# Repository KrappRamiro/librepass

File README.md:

<!-- Improved compatibility of volver arriba link: See: https://github.com/othneildrew/Best-README-Template/pull/73 -->

<!--
*** Thanks for checking out the Best-README-Template. If you have a suggestion
*** that would make this better, please fork the repo and create a pull request
*** or simply open an issue with the tag "enhancement".
*** Don't forget to give the project a star!
*** Thanks again! Now go create something AMAZING! :D
-->

<!-- PROJECT SHIELDS -->
<!--
*** I'm using markdown "reference style" links for readability.
*** Reference links are enclosed in brackets [ ] instead of parentheses ( ).
*** See the bottom of this document for the declaration of the reference variables
*** for contributors-url, forks-url, etc. This is an optional, concise syntax you may use.
*** https://www.markdownguide.org/basic-syntax/#reference-style-links
-->

[![Contributors][contributors-shield]][contributors-url]
[![Forks][forks-shield]][forks-url]
[![Stargazers][stars-shield]][stars-url]
[![Issues][issues-shield]][issues-url]
[![MIT License][license-shield]][license-url]
[![LinkedIn][linkedin-shield]][linkedin-url]

<!-- PROJECT LOGO -->
<br />
<div align="center">

<h1 align="center">Librepass</h1>
  <h2 align="center"> Un sistema de seguridad electrónico </h2>
    <a href="http://librepass-env.us-east-1.elasticbeanstalk.com/">Ver Demo</a>
    ·
    <a href="https://github.com/KrappRamiro/librepass/issues">Reportar un bug</a>
    ·
    <a href="https://github.com/KrappRamiro/librepass/issues">Pedir una función</a>
		<br>
		<br>
</div>

<!-- TABLE OF CONTENTS -->

- [Acerca del Proyecto](#acerca-del-proyecto)
  - [Hecho con](#hecho-con)
- [Antes de Arrancar](#antes-de-arrancar)
  - [Prerequisitos](#prerequisitos)
  - [Instalación](#instalación)
- [Uso](#uso)
  - [Creacion de cuenta e inicio de sesion](#creacion-de-cuenta-e-inicio-de-sesion)
  - [Añadido de empleados y puertas](#añadido-de-empleados-y-puertas)
  - [Visualización de datos](#visualización-de-datos)
- [Tareas a futuro](#tareas-a-futuro)
- [Contribuir](#contribuir)
- [Licencia](#licencia)
- [Contacto](#contacto)
- [FAQ](#faq)
  - [OperationalError Al correr el programa](#operationalerror-al-correr-el-programa)
  - [No puedo borrar empleados y puertas](#no-puedo-borrar-empleados-y-puertas)
  - [Como cerrar sesión](#como-cerrar-sesión)

<!-- ABOUT THE PROJECT -->

## Acerca del Proyecto

<div align="middle">

[![Product Screenshot][product-screenshot]](/webapp/static/images/hero.png)

</div>

Librepass es un sistema integral de control de acceso hecho con ESP32 y tecnologias web en la nube.
El mismo permite controlar el acceso de los empleados a distintos sectores usando tecnología RFID.

En este sistema, se tiene una unidad de acceso por cada puerta, la cual tiene un lector RFID conectado a un ESP32. Este lee cuando se apoya una tarjeta RFID, y deja pasar a los usuarios que esten autorizados, y rechazan a los que no esten autorizados.
Esta autorización es independiente por puerta, y se hace consultando a un backend en Flask que esta corriendo el AWS IOT.

Librepass cuenta tambien con un frontend hecho en Bootstrap apto para dispositivos desktop y mobile, el cual permite a un administrador modificar los permisos de acceso de cada puerta, y ver un historial general y especifico de los accesos.

<p align="right">(<a href="#readme-top">volver arriba</a>)</p>

### Hecho con

- [![Bootstrap][bootstrap.com]][bootstrap-url]
- [![Flask][flask.com]][flask-url]
- [![Arduino][arduino.com]][arduino-url]
- [![Nunjucks][nunjucks.com]][nunjucks-url]
- [![Jinja][jinja.com]][jinja-url]
- [![AWS][aws.com]][aws-url]
- [![Postgres][postgres.com]][postgres-url]

<p align="right">(<a href="#readme-top">volver arriba</a>)</p>

<!-- GETTING STARTED -->

## Antes de Arrancar

Para tener una copia local corriendo, sigue los siguientes pasos

### Prerequisitos

Se necesita el siguiente software para correr el programa

- Python 3.10

- Docker

### Instalación

1. Clona el repositorio

```sh
git clone https://github.com/KrappRamiro/librepass.git
```

2. Instala los paquetes python

```sh
pip install -r requirements.txt
```

3. Para el desarollo local, corre una instancia de docker con el siguiente comando

```sh
sudo docker run --name librepass-postgres -p 5432:5432     -e POSTGRES_USER=librepass -e POSTGRES_PASSWORD=complexpassword123     -e POSTGRES_DB=librepass -d postgres
```

4. Ejecuta el archivo `init_db.py`

```sh
./init_db.py
```

5. Corre el programa

```sh
./app.py
```

6. Abre el programa en tu navegador web en <a href="http://127.0.0.1:5000"> http://127.0.0.1:5000 </a>

<p align="right">(<a href="#readme-top">volver arriba</a>)</p>

<!-- USAGE EXAMPLES -->

## Uso

### Creacion de cuenta e inicio de sesion

Para iniciar con Librepass, lo primero que hay que hacer es crearse una cuenta, tocando en el boton que dice **Registrate**

A continuación, rellená los datos y tocá en el boton azul que dice Registrarse.
Haciendo eso, **ya creaste tu cuenta**

Luego, inicia sesión llenando tu usuario y contraseña.

### Añadido de empleados y puertas

Para añadir empleados y/o puertas, hay que tocar en el boton **Añadir** de la parte superior de la página, y luego en Empleado o Puerta

Luego hay que rellenar los datos correspondientes, y tocar en el boton **Añadir Empleado/Puerta**

### Visualización de datos

Para ver los datos, hay que tocar en el boton **Listas** de la parte superior de la página, y luego en Empleados, Puertas o Accesos, segun se quiera

Aquí se pueden ver los datos. En la columna de acciones, se pueden realizar multiples acciones asociadas a la información que se está viendo

<!-- _For more examples, please refer to the [Documentation](https://example.com)_ -->

<p align="right">(<a href="#readme-top">volver arriba</a>)</p>

<!-- ROADMAP -->

## Tareas a futuro

- [x] Agregar un footer
- [x] Agregar una página para ver todos los accesos de una puerta en específico
  - [ ] A esa página, agregarle un contador (lo mismo para la de Empleados)
- [x] Reformar la interfaz de agregado de empleados y puertas
- [ ] Agregar un modo oscuro
- [ ] Poder ordenar las variables de las tablas de mayor a menor
- [ ] Poder setear la zona horaria

Mira los [open issues](https://github.com/KrappRamiro/librepass/issues) para una lista de todas las funciones propuestas (y todos los errores conocidos)

<p align="right">(<a href="#readme-top">volver arriba</a>)</p>

<!-- CONTRIBUTING -->

## Contribuir

Las contribuciones son lo que hace que la comunidad de código abierto sea un lugar increíble para aprender, inspirar y crear. Cualquier contribución que hagas es **muy apreciada**.

Si tenes una sugerencia que mejoraría el programa, hace un fork del repositorio y crea una pull request. También podes abrir un issue con la etiqueta "mejoras".

¡No olvides darle una estrella al proyecto! ¡Gracias de nuevo!

1. Hace un fork del proyecto

2. Crea tu porpia feature branch (`git checkout -b feature/UnaSuperFeature`)

3. Hace un commit de tus cambios (`git commit -m 'Add some AmazingFeature'`)

4. Pushea a la branch (`git checkout -b feature/AmazingFeature`)

5. Abrí una pull request

<p align="right">(<a href="#readme-top">volver arriba</a>)</p>

<!-- LICENSE -->

## Licencia

Distribuido con la licencia MIT. Ver `LICENSE.txt` para más información

<p align="right">(<a href="#readme-top">volver arriba</a>)</p>

<!-- CONTACT -->

## Contacto

Krapp Ramiro - krappramiro@disroot.org

Project Link: [https://github.com/KrappRamiro/librepass](https://github.com/KrappRamiro/librepass)

<p align="right">(<a href="#readme-top">volver arriba</a>)</p>

<!-- ACKNOWLEDGMENTS -->

## FAQ

### OperationalError Al correr el programa

Si al correr app.py tienes el siguiente error:

```
sqlalchemy.exc.OperationalError: (psycopg2.OperationalError) connection to server at "localhost" (::1), port 5432 failed: Connection refused
	Is the server running on that host and accepting TCP/IP connections?
connection to server at "localhost" (127.0.0.1), port 5432 failed: Connection refused
	Is the server running on that host and accepting TCP/IP connections?
```

Significa que tenes que correr la instancia de docker. Si todavia no la creaste, hacelo usando

```sh
sudo docker run --name librepass-postgres -p 5432:5432     -e POSTGRES_USER=librepass -e POSTGRES_PASSWORD=complexpassword123     -e POSTGRES_DB=librepass -d postgres
```

Si ya corriste ese comando con anterioridad, intenta iniciandola con `sudo docker start librepass-postgres`

### No puedo borrar empleados y puertas

Esa funcion esta temporalmente desactivada

### Como cerrar sesión

Para cerrar sesion, hay que tocar el boton que dice **Cerrar Sesion** arriba a la derecha

<p align="right">(<a href="#readme-top">volver arriba</a>)</p>

<!-- MARKDOWN LINKS & IMAGES -->
<!-- https://www.markdownguide.org/basic-syntax/#reference-style-links -->

[contributors-shield]: https://img.shields.io/github/contributors/KrappRamiro/librepass.svg?style=for-the-badge
[contributors-url]: https://github.com/KrappRamiro/librepass/graphs/contributors
[forks-shield]: https://img.shields.io/github/forks/KrappRamiro/librepass.svg?style=for-the-badge
[forks-url]: https://github.com/KrappRamiro/librepass/network/members
[stars-shield]: https://img.shields.io/github/stars/KrappRamiro/librepass.svg?style=for-the-badge
[stars-url]: https://github.com/KrappRamiro/librepass/stargazers
[issues-shield]: https://img.shields.io/github/issues/KrappRamiro/librepass.svg?style=for-the-badge
[issues-url]: https://github.com/KrappRamiro/librepass/issues
[license-shield]: https://img.shields.io/github/license/KrappRamiro/librepass.svg?style=for-the-badge
[license-url]: https://github.com/KrappRamiro/librepass/blob/master/LICENSE.txt
[linkedin-shield]: https://img.shields.io/badge/-LinkedIn-black.svg?style=for-the-badge&logo=linkedin&colorB=555
[linkedin-url]: https://linkedin.com/in/ramiro-krapp
[product-screenshot]: /webapp/static/images/hero.png
[next.js]: https://img.shields.io/badge/next.js-000000?style=for-the-badge&logo=nextdotjs&logoColor=white
[next-url]: https://nextjs.org/
[react.js]: https://img.shields.io/badge/React-20232A?style=for-the-badge&logo=react&logoColor=61DAFB
[react-url]: https://reactjs.org/
[vue.js]: https://img.shields.io/badge/Vue.js-35495E?style=for-the-badge&logo=vuedotjs&logoColor=4FC08D
[vue-url]: https://vuejs.org/
[angular.io]: https://img.shields.io/badge/Angular-DD0031?style=for-the-badge&logo=angular&logoColor=white
[angular-url]: https://angular.io/
[svelte.dev]: https://img.shields.io/badge/Svelte-4A4A55?style=for-the-badge&logo=svelte&logoColor=FF3E00
[svelte-url]: https://svelte.dev/
[laravel.com]: https://img.shields.io/badge/Laravel-FF2D20?style=for-the-badge&logo=laravel&logoColor=white
[laravel-url]: https://laravel.com
[bootstrap.com]: https://img.shields.io/badge/Bootstrap-563D7C?style=for-the-badge&logo=bootstrap&logoColor=white
[bootstrap-url]: https://getbootstrap.com
[jquery.com]: https://img.shields.io/badge/jQuery-0769AD?style=for-the-badge&logo=jquery&logoColor=white
[jquery-url]: https://jquery.com
[flask.com]: https://img.shields.io/badge/Flask-2c3844?style=for-the-badge&logo=flask
[flask-url]: https://flask.palletsprojects.com/en/2.2.x/
[arduino.com]: https://img.shields.io/badge/Arduino-18bcbf?style=for-the-badge&logo=arduino
[arduino-url]: https://www.arduino.cc/
[nunjucks.com]: https://img.shields.io/badge/Nunjucks-398339?style=for-the-badge&logo=nunjucks
[nunjucks-url]: https://mozilla.github.io/nunjucks/
[jinja.com]: https://img.shields.io/badge/Jinja2-35495E?style=for-the-badge&logo=jinja
[jinja-url]: https://palletsprojects.com/p/jinja/
[aws.com]: https://img.shields.io/badge/AWS-EB5F07?style=for-the-badge&logo=amazon
[aws-url]: https://aws.amazon.com/
[postgres.com]: https://img.shields.io/badge/PostgreSQL-e8dcdc?style=for-the-badge&logo=postgresql
[postgres-url]: https://www.postgresql.org/

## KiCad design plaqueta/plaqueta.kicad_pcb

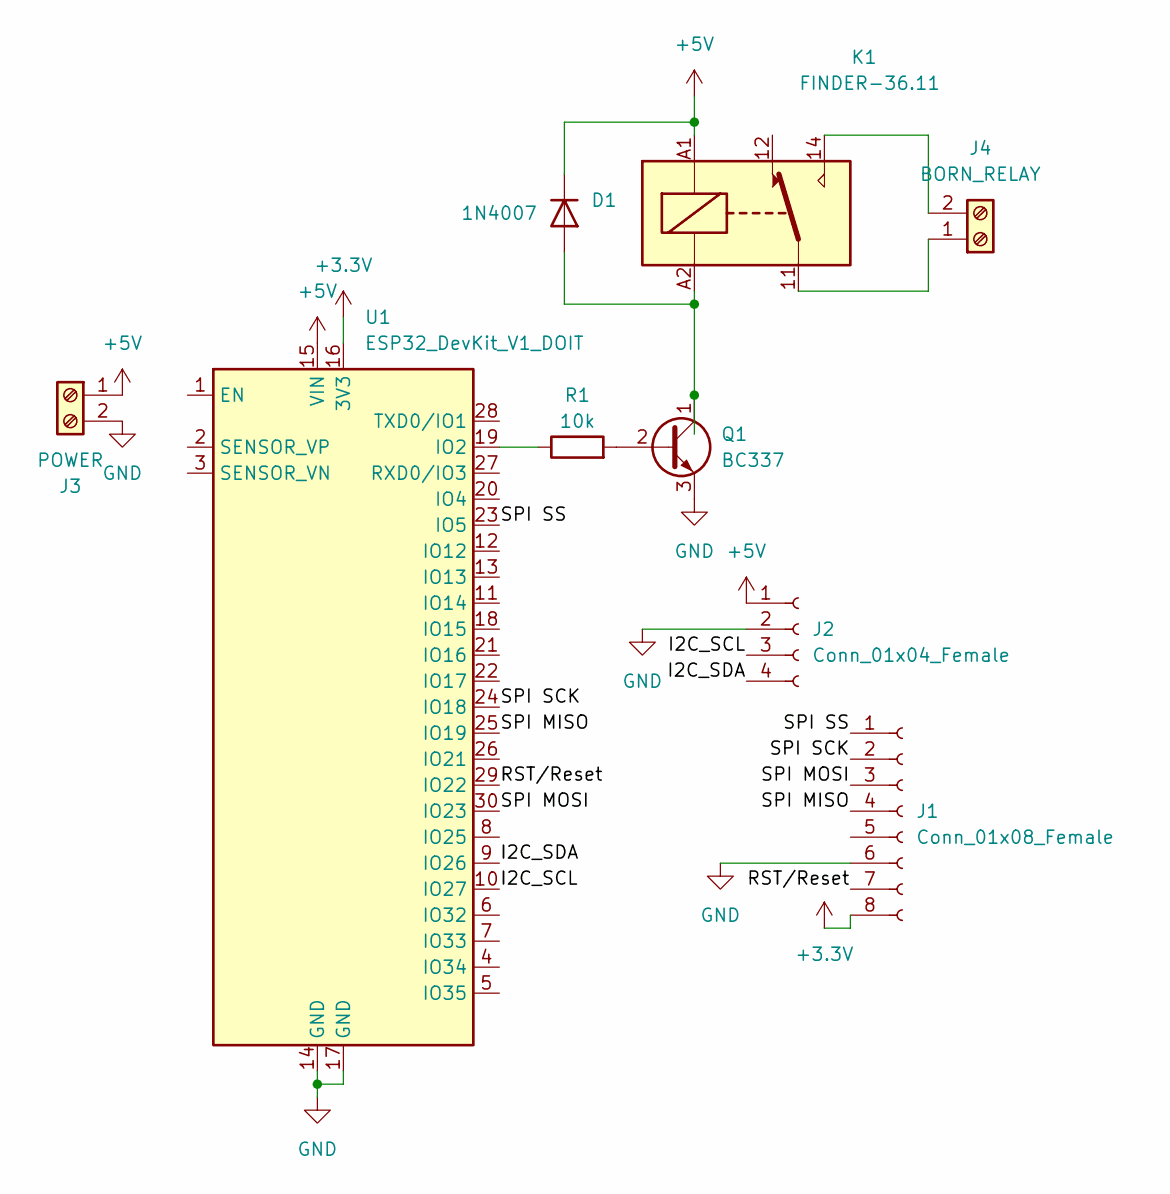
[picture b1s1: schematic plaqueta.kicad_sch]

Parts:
D1: 1N4007; D_DO-41_SOD81_P10.16mm_Horizontal
J1: Conn_01x08_Female; PinSocket_1x08_P2.54mm_Vertical
J2: Conn_01x04_Female; PinSocket_1x04_P2.54mm_Vertical
J3: POWER; tblock_2x1
J4: BORN_RELAY; tblock_2x1
K1: FINDER-36.11; Relay_SPDT_Finder_36.11
Q1: BC337; krapp-TO-92_HandSolder
R1: 10k; krapp-res-generic
U1: ESP32_DevKit_V1_DOIT; esp32_devkit_v1_doit

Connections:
+3.3V: J1.8, U1.16 (3V3)
+5V: D1.1 (K), J2.1, J3.1, K1.A1, U1.15 (VIN)
/I2C_SCL: J2.3, U1.10 (IO27)
/I2C_SDA: J2.4, U1.9 (IO26)
/RST/Reset: J1.7, U1.29 (IO22)
/SPI MISO: J1.4, U1.25 (IO19)
/SPI MOSI: J1.3, U1.30 (IO23)
/SPI SCK: J1.2, U1.24 (IO18)
/SPI SS: J1.1, U1.23 (IO5)
GND: J1.6, J2.2, J3.2, Q1.3 (E), U1.14 (GND), U1.17 (GND)
unnamed: D1.2 (A), K1.A2, Q1.1 (C)
unnamed: J4.1, K1.11
unnamed: J4.2, K1.14
unnamed: Q1.2 (B), R1.2
unnamed: R1.1, U1.19 (IO2)

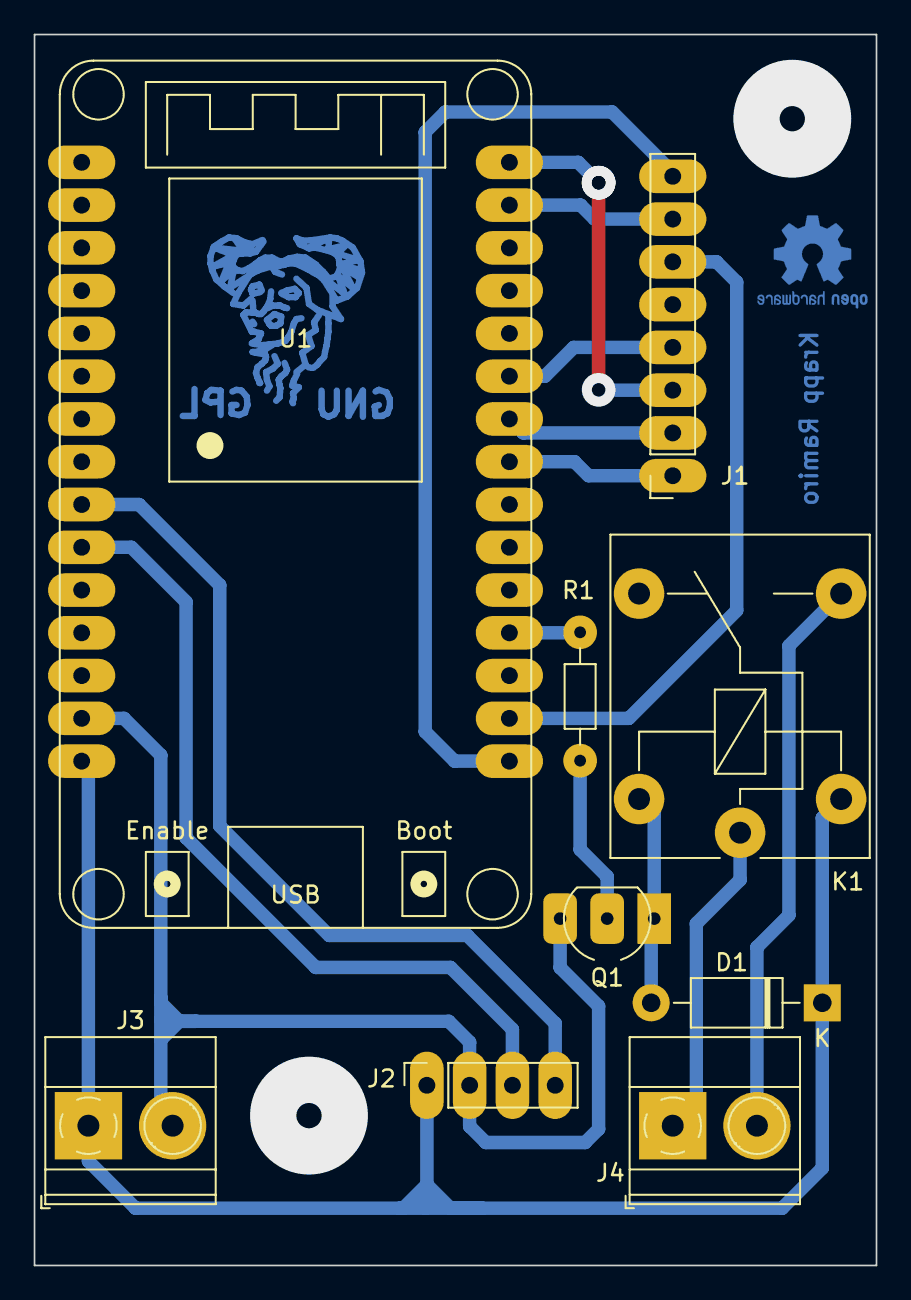
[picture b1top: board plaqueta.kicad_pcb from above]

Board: 2 copper layers, 50.0 x 73.1 mm, 9 parts (0 on the bottom side), 15 nets.

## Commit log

2022-03-24 Inicialización del proyecto con platformIO
2022-03-24 añadida licencia, readme, e inicio del informe
2022-03-24 creado un archivo main.cpp, con un sistema prototipo de como va a ser la organizacion entre clases
2022-03-26 agregado diagrama de drawio
2022-03-26 añadido codigo de prueba para el RFID
2022-03-27 eliminada seccion erronea base de datos del informe
2022-03-27 dividido el informe en subfiles
2022-03-28 actualizado el informe y pasada portada a subfile
2022-03-30 actualizado informe, agregada bibliografia y comienzo informe EDPL
    agregue la bibliografia en un archivo .bib, agregue multiples imagenes, e hice una gran parte de la seccion del protocolo SPI, ademas comencé con la parte del sistema RFID
2022-03-30 añadidos los ultimos cambios antes del fork
2022-03-30 cambiado el enfoque del proyecto
2022-03-30 adaptado main.cpp a nuevo enfoque
2022-04-01 actualizada la bitacora y partes-proyecto.tex
2022-04-02 traducidos comentarios al español, eliminada funcion writingData(), agregada funcion getUID()
2022-04-04 añadidos getters, getUserStringSerialInput(), organizados includes y comentarios
2022-04-05 añadido constructor de Empleado, array misEmpleados, añadida funcion createEmployee
2022-04-07 cambiado diagrama-esquematico.tex por diagrama-bloques.tex, actualizada bibliografia y bitacoras, agregada licencia
2022-04-08 solucionado problema con logging, no llegue a hacer del webserver en esta branch
2022-04-17 añadido un webserver que tira valores de hora y temperatura
2022-04-17 correccion del funcionamiento de la fecha y hora en el webserver
2022-04-17 correccion de readme
2022-04-17 añadidos comentarios
2022-04-19 actualizado informe
    agregada informacion del ESP32, del framework arduino, del server asincronico, correcion de diagrama-bloques y diagrama-esquematico
2022-04-19 actualizadas las bitacoras
2022-05-17 Creados forms para envio de datos desde cliente a servidor
    Use unos forms en el html para mandar datos desde el cliente, y arme un
    codigo en el servidor para recibir cada uno de esos inputs, y que por
    ahora los Serial.printee
2022-05-19 divido el codigo en un header de funciones y un main
2022-05-19 puesta la clase Empleado en un archivo aparte
2022-05-19 añadido un pragma region a la parte con el codigo html
2022-06-28 actualizado informe epdl y diagrama
2022-06-29 arreglado error con bibliografia y actualizado diagrama
2022-06-30 actualizada bitacora
2022-06-30 actualizada bibliografia
2022-06-30 actualizado diagrama, bitacoras y bibliografia
2022-08-31 added elastic beanstalk
2022-09-01 disabled the database creation on aws
2022-09-01 changes 01_flask_config
2022-09-01 updated 01_flask_config
2022-09-02 updated aws deploy
2022-09-02 updated aws deploy 2
2022-09-17 added index, Users, db_models and forms, also added templates
2022-09-19 added empleados, puertas, edits and deletes
2022-09-20 changed variable names from spanish to english
2022-09-20 added requirements.txt
2022-09-20 removed unwanted files
2022-09-21 added the use of bootstrap
2022-09-22 updated webpage
2022-10-03 added the ESP32 client with API requests to the webapp
2022-10-10 added OLED screen and updated informe with the code
2022-10-16 updates for eb
2022-10-16 realizados pequeños cambios esteticos
2022-10-16 fixed bug where navbar on mobile was not 100% width
2022-10-17 undid last commit changes
2022-10-17 added page to see all the accesses from an specific employee
2022-10-17 added footer and removed redundancy in html
2022-10-17 added favicon
2022-10-17 added github link to navbar
2022-10-17 added a hero to index
2022-10-17 stylized the hero
2022-10-17 fixed overflow of hero image on mobile
2022-10-17 stylized the login page
2022-10-17 stylized the register page
2022-10-17 added thumbnail
2022-10-19 agregado readme
2022-10-20 actualizado el informe
2022-10-20 actualizado readme
2022-11-08 updated informe
2023-03-30 fixed error in readme
